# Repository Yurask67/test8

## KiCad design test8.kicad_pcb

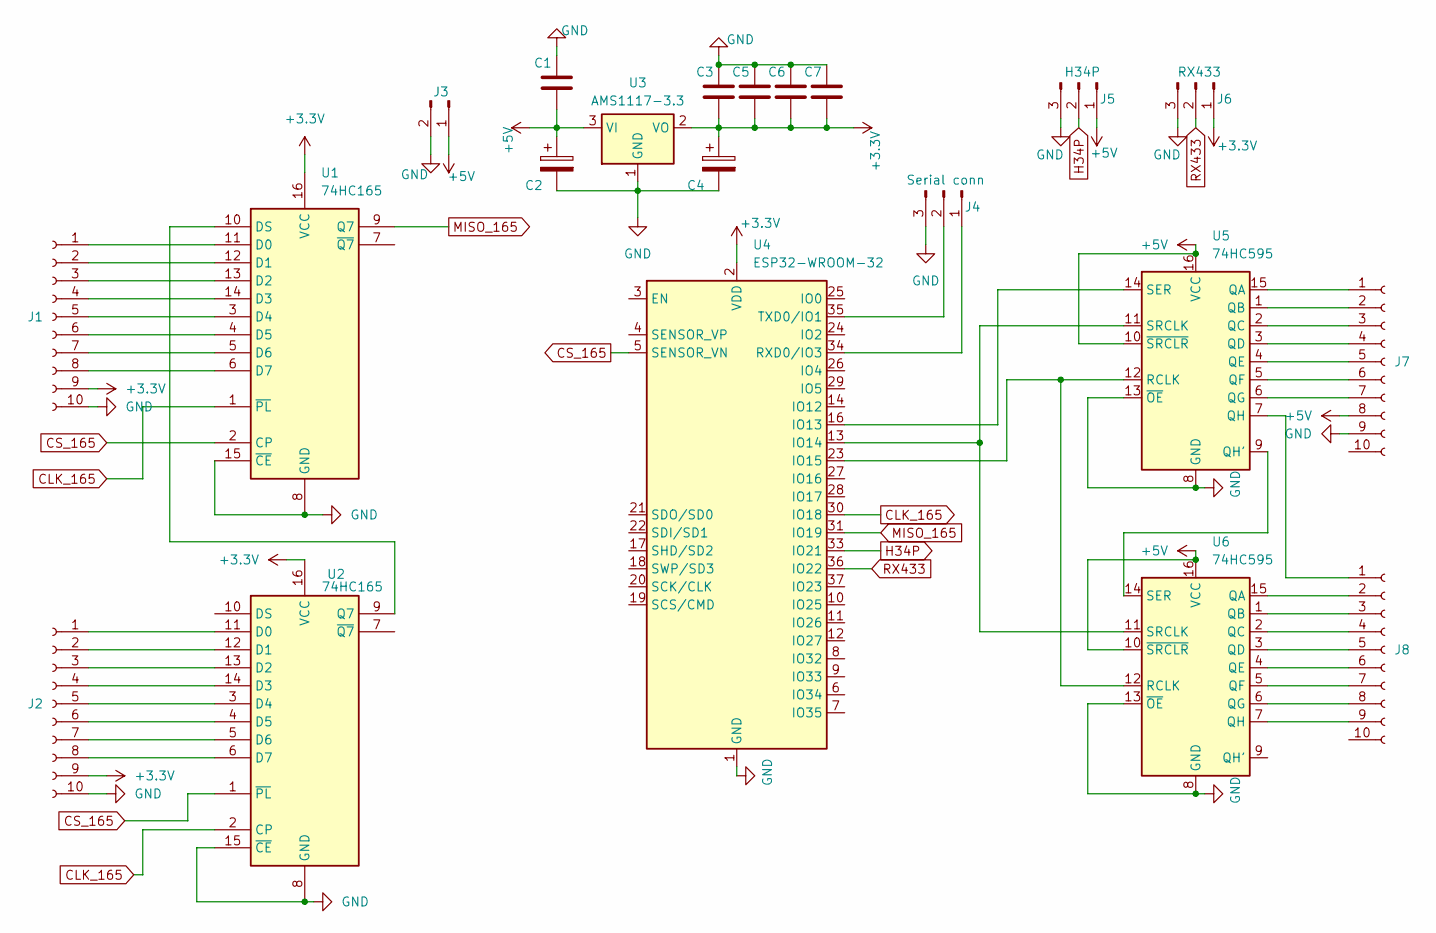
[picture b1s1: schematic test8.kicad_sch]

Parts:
C1, C3, C5, C6, C7: C; C_0805_2012Metric
C2, C4: C_Polarized; CP_Radial_D10.0mm_P5.00mm
J1, J2, J7, J8: Conn_01x10_Socket; PinHeader_2x05_P2.00mm_Vertical
J3: Conn_01x02_Pin; PinHeader_1x02_P2.54mm_Vertical
J4, J5, J6: Conn_01x03_Pin; PinSocket_1x03_P2.00mm_Vertical
U1, U2: 74HC165; SOP-16_4.55x10.3mm_P1.27mm
U3: AMS1117-3.3; SOT-223-3_TabPin2
U4: ESP32-WROOM-32
U5, U6: 74HC595; DIP-16_W7.62mm_LongPads

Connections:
+3.3V: C3.2, C4.1, C5.2, C6.2, C7.2, J1.9, J2.9, J6.1, U1.16 (VCC), U2.16 (VCC), U3.2 (VO), U3.2@1, U4.2 (VDD)
+5V: C1.2, C2.1, J3.1, J5.1, J7.8, U3.3 (VI), U5.10 (~SRCLR), U5.16 (VCC), U6.10 (~SRCLR), U6.16 (VCC)
CLK_165: U1.1 (~PL), U2.2 (CP), U4.30 (IO18)
CS_165: U1.2 (CP), U2.1 (~PL), U4.5 (SENSOR_VN)
GND: C1.1, C2.2, C3.1, C4.2, C5.1, C6.1, C7.1, J1.10, J2.10, J3.2, J4.3, J5.3, J6.3, J7.9, U1.8 (GND), U1.15 (~CE), U2.8 (GND), U2.15 (~CE), U3.1 (GND), U4.1 (GND), U4.38 (GND), U5.8 (GND), U5.13 (~OE), U6.8 (GND), U6.13 (~OE)
H34P: J5.2, U4.33 (IO21)
MISO_165: U1.9 (Q7), U4.31 (IO19)
unnamed: J1.1, U1.11 (D0)
unnamed: J1.2, U1.12 (D1)
unnamed: J1.3, U1.13 (D2)
unnamed: J1.4, U1.14 (D3)
unnamed: J1.5, U1.3 (D4)
unnamed: J1.6, U1.4 (D5)
unnamed: J1.7, U1.5 (D6)
unnamed: J1.8, U1.6 (D7)
unnamed: J2.1, U2.11 (D0)
unnamed: J2.2, U2.12 (D1)
unnamed: J2.3, U2.13 (D2)
unnamed: J2.4, U2.14 (D3)
unnamed: J2.5, U2.3 (D4)
unnamed: J2.6, U2.4 (D5)
unnamed: J2.7, U2.5 (D6)
unnamed: J2.8, U2.6 (D7)
unnamed: J4.1, U4.34 (RXD0/IO3)
unnamed: J4.2, U4.35 (TXD0/IO1)
unnamed: J7.1, U5.15 (QA)
unnamed: J7.2, U5.1 (QB)
unnamed: J7.3, U5.2 (QC)
unnamed: J7.4, U5.3 (QD)
unnamed: J7.5, U5.4 (QE)
unnamed: J7.6, U5.5 (QF)
unnamed: J7.7, U5.6 (QG)
unnamed: J8.1, U5.7 (QH)
unnamed: J8.2, U6.15 (QA)
unnamed: J8.3, U6.1 (QB)
unnamed: J8.4, U6.2 (QC)
unnamed: J8.5, U6.3 (QD)
unnamed: J8.6, U6.4 (QE)
unnamed: J8.7, U6.5 (QF)
unnamed: J8.8, U6.6 (QG)
unnamed: J8.9, U6.7 (QH)
unnamed: U1.10 (DS), U2.9 (Q7)
unnamed: U4.16 (IO13), U5.14 (SER)
unnamed: U4.13 (IO14), U5.11 (SRCLK), U6.11 (SRCLK)
unnamed: U4.23 (IO15), U5.12 (RCLK), U6.12 (RCLK)
unnamed: U5.9 (QH'), U6.14 (SER)
RX433: J6.2, U4.36 (IO22)

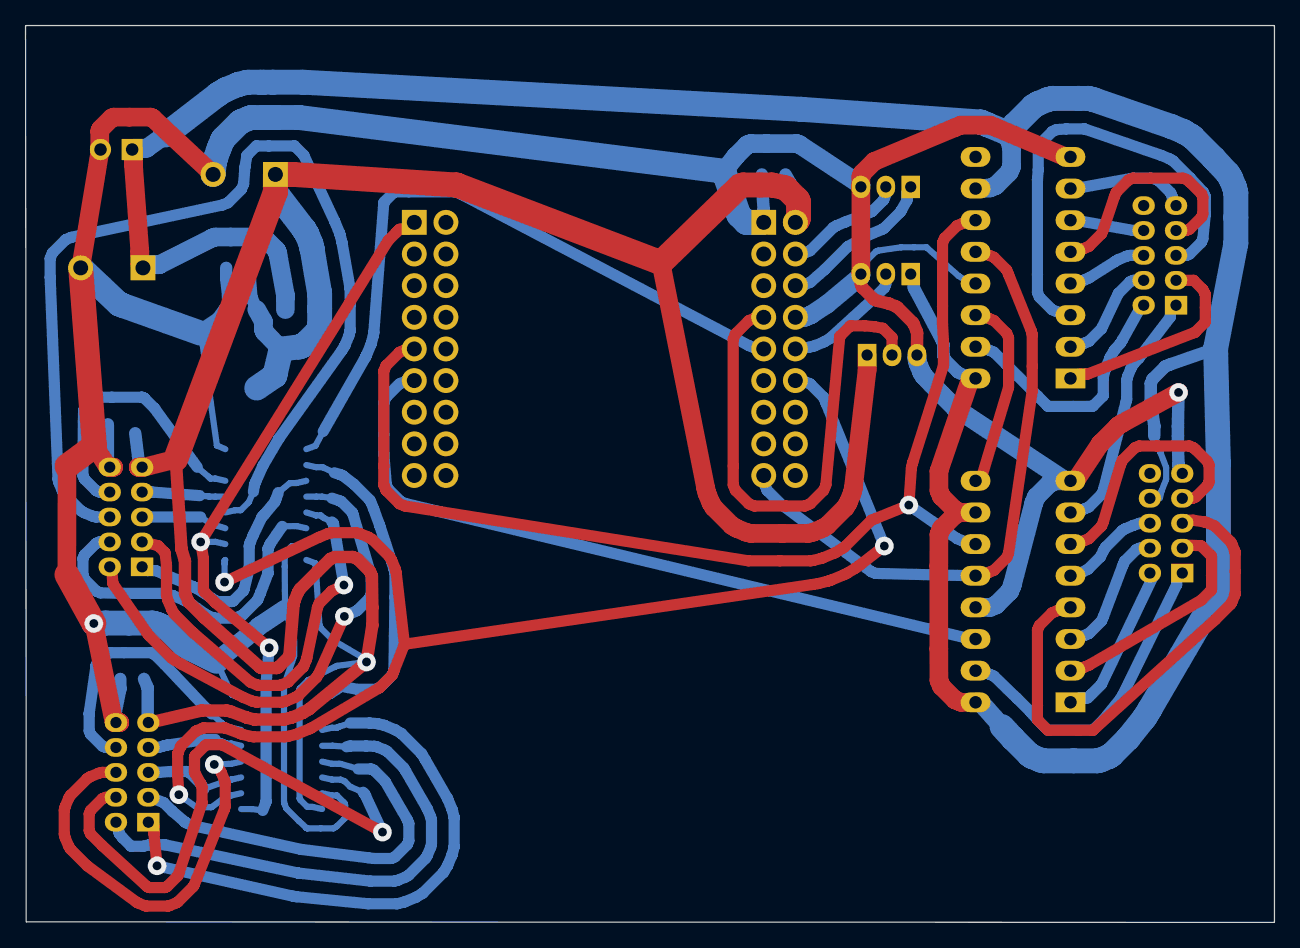
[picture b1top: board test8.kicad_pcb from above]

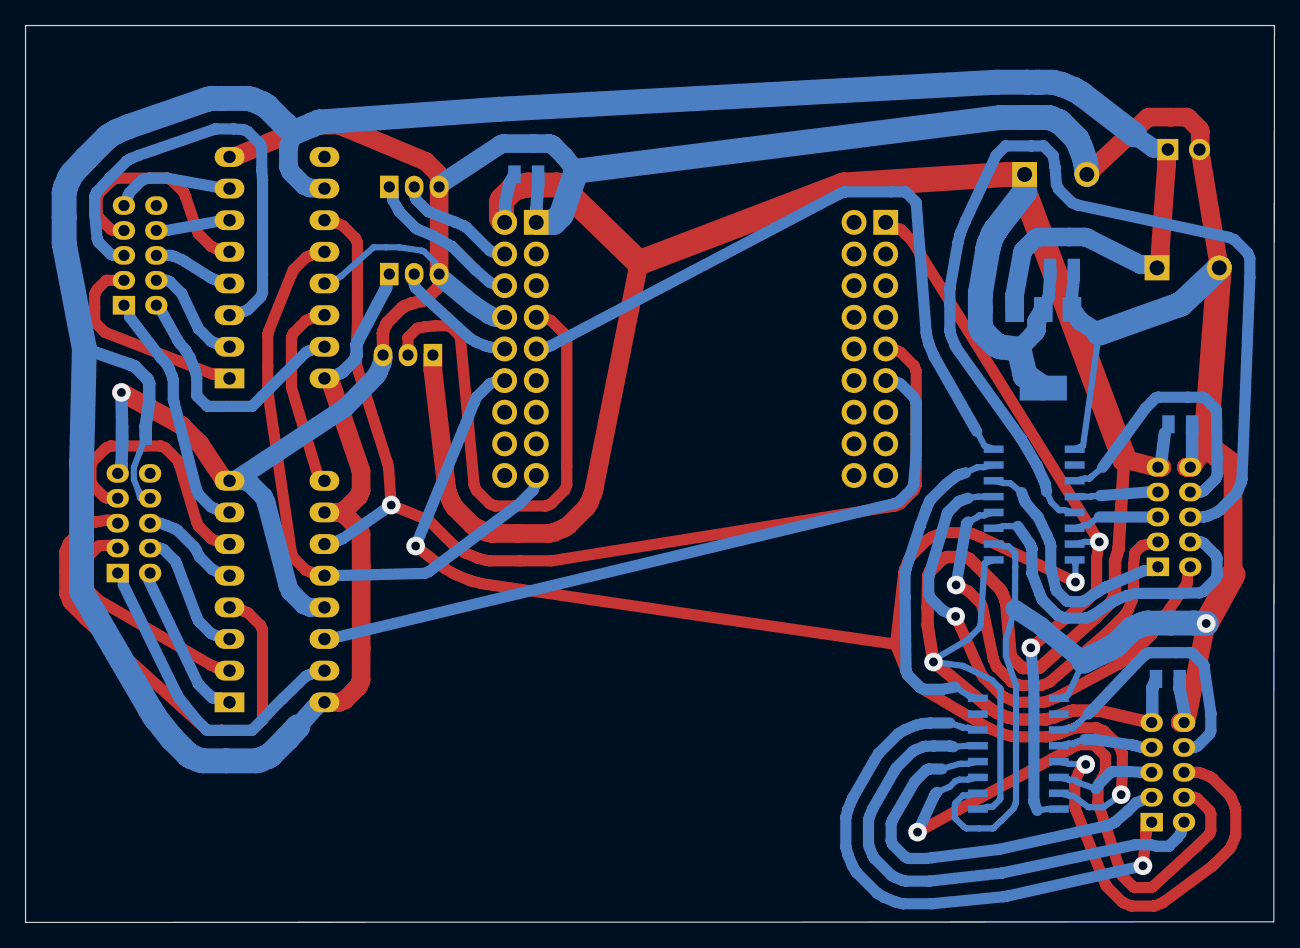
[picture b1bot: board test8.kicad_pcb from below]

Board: 2 copper layers, 100.3 x 72.0 mm, 21 parts (8 on the bottom side), 47 nets.

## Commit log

2025-02-05 start
    start
2025-02-05 gitignore add
2025-02-05 esp32wrom process
2025-02-05 process
2025-02-09 вариант 1
2025-02-10 Topor+595+165
2025-02-10 595+165+topor
2025-02-12 Граница ПП изм слой
2025-02-24 Kikad 9
2025-02-25 исправлены разъемы 2мм на 2,54
